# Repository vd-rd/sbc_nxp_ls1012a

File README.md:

# sbc-ls1012a
NXP Layerscape LS1012A

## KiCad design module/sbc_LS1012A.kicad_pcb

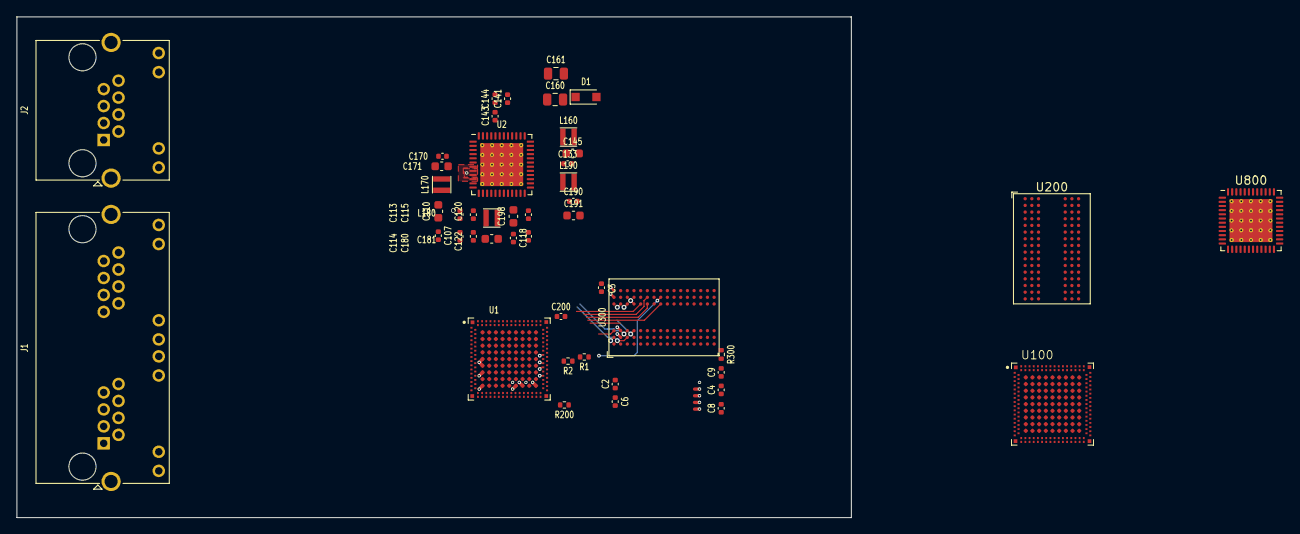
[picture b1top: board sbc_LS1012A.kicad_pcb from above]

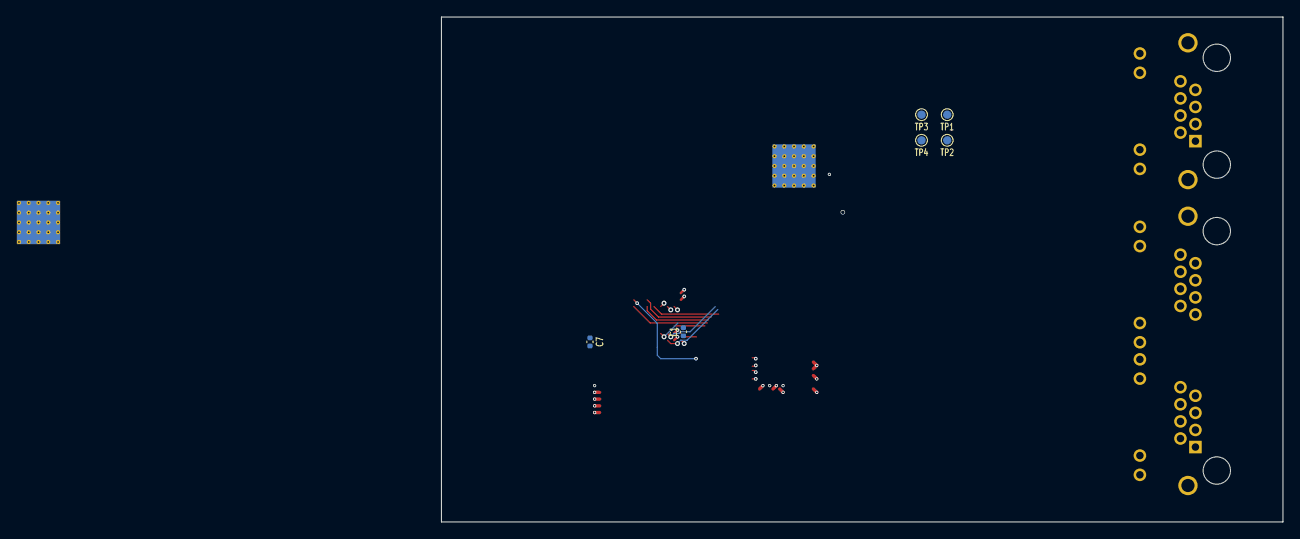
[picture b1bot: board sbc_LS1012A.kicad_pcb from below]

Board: 4 copper layers, 100.0 x 60.0 mm, 52 parts (6 on the bottom side), 87 nets.

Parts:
C1, C2, C3, C4, C9, C107, C118, C170, C180, C190, C200: 100nF; C_0402_1005Metric
C6, C7, C8, C113, C141, C143: 1uF; C_0402_1005Metric
C110, C171, C181, C191, C198: 4.7uF; C_0603_1608Metric
C114, C115, C120, C122, C133: 2.2uF; C_0402_1005Metric
C144: 220nF; C_0402_1005Metric
C145: 10uF; C_0603_1608Metric
C160, C161: 22uF; C_0805_2012Metric
D1: D_Schottky; D_SOD-323_HandSoldering
J1: RJ45_LED_Shielded_x2; RJ45_Amphenol_RJHSE538X-02
J2: RJ45_LED; RJ45_Amphenol_RJHSE538X
L160, L170, L180, L190: 1.5uH; L_Taiyo-Yuden_NR-20xx
R1, R2: 10; R_0402_1005Metric
R200, R300: 240; R_0402_1005Metric
TP1, TP2, TP3, TP4: TestPoint; TestPoint_Pad_D1.0mm
U1, U100: LS1012A; NXP_LS1012ASE7EKA
U2, U800: VR5100; QFN-48-1EP_7x7mm_P0.5mm_EP5.15x5.15mm_ThermalVias
U200, U300: MT41K512M16HA; BGA-96_9.0x13.0mm_Layout2x3x16_P0.8mm

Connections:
+3V3: C107.1, C110.1, C113.1, C118.1, C145.1, C198.1, L160.2, U2.7 (PVIN1), U2.10 (PVIN1), U2.13 (VLDOIN1), U2.16 (VLDOIN2), U2.18 (PVIN2), U2.21 (VLDOIN34), U2.28 (PVIN3), U2.38 (PVIN2), U2.42 (VIN), U800.7 (PVIN1), U800.10 (PVIN1), U800.13 (VLDOIN1), U800.16 (VLDOIN2), U800.18 (PVIN2), U800.21 (VLDOIN34), U800.28 (PVIN3), U800.38 (PVIN2), U800.42 (VIN)
/power/LDO2: C115.1, U2.15 (LDO2), U800.15 (LDO2)
/power/LDO3: C120.1, U2.20 (LDO3), U800.20 (LDO3)
/power/LDO4: C122.1, U2.22 (LDO4), U800.22 (LDO4)
/power/VDD_SFP: C114.1, U2.14 (LDO1), U800.14 (LDO1)
/power/lx1: L170.1, U2.8 (LX1), U2.9 (LX1), U800.8 (LX1), U800.9 (LX1)
/power/vr_vcc: C141.1, U2.41 (VCC), U800.41 (VCC)
/sdram/addr0: U1.103 (D1_MA00), U100.103 (D1_MA00), U200.N3 (A0), U300.N3 (A0)
/sdram/addr1: U1.37 (D1_MA01), U100.37 (D1_MA01), U200.P7 (A1), U300.P7 (A1)
/sdram/addr2: U1.102 (D1_MA02), U100.102 (D1_MA02), U200.P3 (A2), U300.P3 (A2)
/sdram/addr3: U1.97 (D1_MA03), U100.97 (D1_MA03), U200.N2 (A3), U300.N2 (A3)
/sdram/addr4: U1.98 (D1_MA04), U100.98 (D1_MA04), U200.P8 (A4), U300.P8 (A4)
/sdram/addr5: U1.38 (D1_MA05), U100.38 (D1_MA05), U200.P2 (A5), U300.P2 (A5)
/sdram/addr6: U1.34 (D1_MA06), U100.34 (D1_MA06), U200.R8 (A6), U300.R8 (A6)
/sdram/addr7: U1.32 (D1_MA07), U100.32 (D1_MA07), U200.R2 (A7), U300.R2 (A7)
/sdram/addr8: U1.96 (D1_MA08), U100.96 (D1_MA08), U200.T8 (A8), U300.T8 (A8)
/sdram/addr9: U1.100 (D1_MA09), U100.100 (D1_MA09), U200.R3 (A9), U300.R3 (A9)
/sdram/addr10: U1.106 (D1_MA10), U100.106 (D1_MA10), U200.L7 (A10/AP), U300.L7 (A10/AP)
/sdram/addr11: U1.99 (D1_MA11), U100.99 (D1_MA11), U200.R7 (A11), U300.R7 (A11)
/sdram/addr12: U1.40 (D1_MA12), U100.40 (D1_MA12), U200.N7 (A12/~BC), U300.N7 (A12/~BC)
/sdram/addr13: U1.33 (D1_MA13), U100.33 (D1_MA13), U200.T3 (A13), U300.T3 (A13)
/sdram/addr14: U1.31 (D1_MA14), U100.31 (D1_MA14), U200.T7 (A14), U300.T7 (A14)
/sdram/data0: U1.47 (D1_MDQ00), U100.47 (D1_MDQ00), U200.E3 (DQ0), U300.E3 (DQ0)
/sdram/data1: U1.50 (D1_MDQ01), U100.50 (D1_MDQ01), U200.F7 (DQ1), U300.F7 (DQ1)
/sdram/data2: U1.49 (D1_MDQ02), U100.49 (D1_MDQ02), U200.F2 (DQ2), U300.F2 (DQ2)
/sdram/data3: U1.114 (D1_MDQ03), U100.114 (D1_MDQ03), U200.F8 (DQ3), U300.F8 (DQ3)
/sdram/data4: U1.109 (D1_MDQ04), U100.109 (D1_MDQ04), U200.H3 (DQ4), U300.H3 (DQ4)
/sdram/data5: U1.46 (D1_MDQ05), U100.46 (D1_MDQ05), U200.H8 (DQ5), U300.H8 (DQ5)
/sdram/data6: U1.110 (D1_MDQ06), U100.110 (D1_MDQ06), U200.G2 (DQ6), U300.G2 (DQ6)
/sdram/data7: U1.113 (D1_MDQ07), U100.113 (D1_MDQ07), U200.H7 (DQ7), U300.H7 (DQ7)
/sdram/data8: U1.118 (D1_MDQ08), U100.118 (D1_MDQ08), U200.D7 (DQ8), U300.D7 (DQ8)
/sdram/data9: U1.116 (D1_MDQ09), U100.116 (D1_MDQ09), U200.C3 (DQ9), U300.C3 (DQ9)
/sdram/data10: U1.57 (D1_MDQ10), U100.57 (D1_MDQ10), U200.C8 (DQ10), U300.C8 (DQ10)
/sdram/data11: U1.53 (D1_MDQ11), U100.53 (D1_MDQ11), U200.C2 (DQ11), U300.C2 (DQ11)
/sdram/data12: U1.56 (D1_MDQ12), U100.56 (D1_MDQ12), U200.A7 (DQ12), U300.A7 (DQ12)
/sdram/data13: U1.51 (D1_MDQ13), U100.51 (D1_MDQ13), U200.A2 (DQ13), U300.A2 (DQ13)
/sdram/data14: U1.119 (D1_MDQ14), U100.119 (D1_MDQ14), U200.B8 (DQ14), U300.B8 (DQ14)
/sdram/data15: U1.115 (D1_MDQ15), U100.115 (D1_MDQ15), U200.A3 (DQ15), U300.A3 (DQ15)
/sdram/ddr_ba0: U1.101 (D1_MBA0), U100.101 (D1_MBA0), U200.M2 (BA0), U300.M2 (BA0)
/sdram/ddr_ba1: U1.36 (D1_MBA1), U100.36 (D1_MBA1), U200.N8 (BA1), U300.N8 (BA1)
/sdram/ddr_ba2: U1.104 (D1_MBA2), U100.104 (D1_MBA2), U200.M3 (BA2), U300.M3 (BA2)
/sdram/ddr_cas: U1.43 (D1_MCAS_B), U100.43 (D1_MCAS_B), U200.K3 (~CAS), U300.K3 (~CAS)
/sdram/ddr_ck_n: R2.1, U200.K7 (~CK), U300.K7 (~CK)
/sdram/ddr_ck_p: R1.1, U200.J7 (CK), U300.J7 (CK)
/sdram/ddr_cke: U1.42 (D1_MCKE), U100.42 (D1_MCKE), U200.K9 (CKE), U300.K9 (CKE)
/sdram/ddr_cs: U1.41 (D1_MCS_B), U100.41 (D1_MCS_B), U200.L2 (~CS), U300.L2 (~CS)
/sdram/ddr_dm0: U1.112 (D1_MDM0), U100.112 (D1_MDM0), U200.E7 (LDM), U300.E7 (LDM)
/sdram/ddr_dm1: U1.54 (D1_MDM1), U100.54 (D1_MDM1), U200.D3 (UDM), U300.D3 (UDM)
/sdram/ddr_dqs0+: U1.111 (D1_MDQS0), U100.111 (D1_MDQS0), U200.F3 (LDQS), U300.F3 (LDQS)
/sdram/ddr_dqs0-: U1.48 (D1_MDQS0_B), U100.48 (D1_MDQS0_B), U200.G3 (~LDQS), U300.G3 (~LDQS)
/sdram/ddr_dqs1+: U1.117 (D1_MDQS1), U100.117 (D1_MDQS1), U200.C7 (UDQS), U300.C7 (UDQS)
/sdram/ddr_dqs1-: U1.55 (D1_MDQS1_B), U100.55 (D1_MDQS1_B), U200.B7 (~UDQS), U300.B7 (~UDQS)
/sdram/ddr_odt: U1.45 (D1_MODT), U100.45 (D1_MODT), U200.K1 (ODT), U300.K1 (ODT)
/sdram/ddr_ras: U1.108 (D1_MRAS_B), U100.108 (D1_MRAS_B), U200.J3 (~RAS), U300.J3 (~RAS)
/sdram/ddr_we: U1.105 (D1_MWE_B), U100.105 (D1_MWE_B), U200.L3 (~WE), U300.L3 (~WE)
GND: C1.2, C2.2, C3.2, C4.2, C6.2, C7.2, C8.2, C9.2, C107.2, C110.2, C113.2, C114.2, C115.2, C118.2, C120.2, C122.2, C133.2, C141.2, C143.2, C144.2, C145.2, C160.2, C161.2, C170.2, C171.2, C180.2, C181.2, C190.2, C191.2, C198.2, C200.2, R200.1, R300.1, U1.131 (GND), U1.133 (GND), U1.135 (GND), U1.138 (GND), U1.139 (GND), U1.140 (GND), U1.146 (GND), U1.148 (GND), U1.150 (GND), U1.152 (GND), U1.153 (GND), U1.154 (GND), U1.156 (GND), U1.157 (GND), U1.158 (GND), U1.160 (GND), U1.162 (GND), U1.164 (GND), U1.166 (GND), U1.167 (GND), U1.170 (GND), U1.172 (GND), U1.175 (GND), U1.176 (GND), U1.178 (GND), U1.180 (GND), U1.182 (GND), U1.184 (GND), U1.185 (GND), U1.188 (GND), U1.190 (GND), U1.192 (GND), U1.193 (GND), U1.196 (XOSC_GND), U1.197 (SD_GND), U1.201 (SD_GND), U1.202 (GND), U1.203 (GND), U1.208 (SD_GND), U1.210 (GND), U1.211 (GND), U2.5 (ICTEST), U2.12 (SGND), U2.26 (SGND), U2.31 (SGND), U2.39 (VDDOTP), U2.40 (SGND), U2.49 (EP), U100.131 (GND), U100.133 (GND), U100.135 (GND), U100.138 (GND), U100.139 (GND), U100.140 (GND), U100.146 (GND), U100.148 (GND), U100.150 (GND), U100.152 (GND), U100.153 (GND), U100.154 (GND), U100.156 (GND), U100.157 (GND), U100.158 (GND), U100.160 (GND), U100.162 (GND), U100.164 (GND), U100.166 (GND), U100.167 (GND), U100.170 (GND), U100.172 (GND), U100.175 (GND), U100.176 (GND), U100.178 (GND), U100.180 (GND), U100.182 (GND), U100.184 (GND), U100.185 (GND), U100.188 (GND), U100.190 (GND), U100.192 (GND), U100.193 (GND), U100.196 (XOSC_GND), U100.197 (SD_GND), U100.201 (SD_GND), U100.202 (GND), U100.203 (GND), U100.208 (SD_GND), U100.210 (GND), U100.211 (GND), U200.A9 (VSS), U200.B1 (VSSQ), U200.B3 (VSS), U200.B9 (VSSQ), U200.D1 (VSSQ), U200.D8 (VSSQ), U200.E1 (VSS), U200.E2 (VSSQ), U200.E8 (VSSQ), U200.F9 (VSSQ), U200.G1 (VSSQ), U200.G8 (VSS), U200.G9 (VSSQ), U200.J2 (VSS), U200.J8 (VSS), U200.M1 (VSS), U200.M9 (VSS), U200.P1 (VSS), U200.P9 (VSS), U200.T1 (VSS), U200.T9 (VSS), U300.A9 (VSS), U300.B1 (VSSQ), U300.B3 (VSS), U300.B9 (VSSQ), U300.D1 (VSSQ), U300.D8 (VSSQ), U300.E1 (VSS), U300.E2 (VSSQ), U300.E8 (VSSQ), U300.F9 (VSSQ), U300.G1 (VSSQ), U300.G8 (VSS), U300.G9 (VSSQ), U300.J2 (VSS), U300.J8 (VSS), U300.M1 (VSS), U300.M9 (VSS), U300.P1 (VSS), U300.P9 (VSS), U300.T1 (VSS), U300.T9 (VSS), U800.5 (ICTEST), U800.12 (SGND), U800.26 (SGND), U800.31 (SGND), U800.39 (VDDOTP), U800.40 (SGND), U800.49 (EP)
unnamed: C143.1, U2.43 (VDIG), U800.43 (VDIG)
unnamed: C144.1, U2.44 (VBG), U800.44 (VBG)
unnamed: D1.2 (A), L160.1, U2.35 (LXBST), U800.35 (LXBST)
unnamed: L180.1, U2.17 (LX2), U800.17 (LX2)
unnamed: L190.1, U2.29 (LX3), U800.29 (LX3)
unnamed: R1.2, U1.44 (D1_MCK), U100.44 (D1_MCK)
unnamed: R2.2, U1.107 (D1_MCK_B), U100.107 (D1_MCK_B)
unnamed: R200.2, U1.35 (D1_MDIC), U100.35 (D1_MDIC)
unnamed: R300.2, U200.L8 (ZQ), U300.L8 (ZQ)
unnamed: U1.144 (O1VDD), U1.145 (O1VDD), U1.174 (O1VDD)
unnamed: U1.151 (VDD), U1.161 (VDD), U1.163 (VDD), U1.169 (VDD), U1.171 (VDD), U1.179 (VDD), U1.181 (VDD), U1.187 (VDD), U1.189 (VDD), U1.191 (VDD)
unnamed: U1.168 (O2VDD), U1.177 (O2VDD)
unnamed: U1.198 (S1VDD), U1.200 (S1VDD)
unnamed: U1.199 (X1VDD), U1.209 (X1VDD)
unnamed: U100.144 (O1VDD), U100.145 (O1VDD), U100.174 (O1VDD)
unnamed: U100.151 (VDD), U100.161 (VDD), U100.163 (VDD), U100.169 (VDD), U100.171 (VDD), U100.179 (VDD), U100.181 (VDD), U100.187 (VDD), U100.189 (VDD), U100.191 (VDD)
unnamed: U100.168 (O2VDD), U100.177 (O2VDD)
unnamed: U100.198 (S1VDD), U100.200 (S1VDD)
unnamed: U100.199 (X1VDD), U100.209 (X1VDD)
PMIC_I2C_SCL: TP3.1, U2.46 (SCL), U800.46 (SCL)
PMIC_I2C_SDA: TP2.1, U2.45 (SDA), U800.45 (SDA)
PMIC_INTn: TP1.1, U2.1 (INTb), U800.1 (INTb)
RESET: U200.T2 (~RESET), U300.T2 (~RESET)
SDHC_VSEL: TP4.1, U2.2 (SD_VSEL), U800.2 (SD_VSEL)
VCC_1V8: C180.1, C181.1, L180.2, U2.19 (FB2), U2.47 (VCCI2C), U800.19 (FB2), U800.47 (VCCI2C)
VCC_DDR: C1.1, C2.1, C3.1, C4.1, C6.1, C7.1, C8.1, C190.1, C191.1, L190.2, U1.147 (G1VDD), U1.155 (G1VDD), U1.165 (G1VDD), U1.173 (G1VDD), U1.183 (G1VDD), U2.24 (REFIN), U2.27 (FB3), U100.147 (G1VDD), U100.155 (G1VDD), U100.165 (G1VDD), U100.173 (G1VDD), U100.183 (G1VDD), U200.A1 (VDDQ), U200.A8 (VDDQ), U200.B2 (VDD), U200.C1 (VDDQ), U200.C9 (VDDQ), U200.D2 (VDDQ), U200.D9 (VDD), U200.E9 (VDDQ), U200.F1 (VDDQ), U200.G7 (VDD), U200.H2 (VDDQ), U200.H9 (VDDQ), U200.K2 (VDD), U200.K8 (VDD), U200.N1 (VDD), U200.N9 (VDD), U200.R1 (VDD), U200.R9 (VDD), U300.A1 (VDDQ), U300.A8 (VDDQ), U300.B2 (VDD), U300.C1 (VDDQ), U300.C9 (VDDQ), U300.D2 (VDDQ), U300.D9 (VDD), U300.E9 (VDDQ), U300.F1 (VDDQ), U300.G7 (VDD), U300.H2 (VDDQ), U300.H9 (VDDQ), U300.K2 (VDD), U300.K8 (VDD), U300.N1 (VDD), U300.N9 (VDD), U300.R1 (VDD), U300.R9 (VDD), U800.24 (REFIN), U800.27 (FB3)
VCC_DRAM_REF: C200.1, U1.52 (D1_MVREF), U100.52 (D1_MVREF)
VCC_OTG: C160.1, C161.1, D1.1 (K), U2.37 (FBBST), U800.37 (FBBST)
VCC_SD: C133.1, U2.33 (VSD), U800.33 (VSD)
VDD_CORE: C170.1, C171.1, L170.2, U2.6 (FB1), U800.6 (FB1)
VREF_DDR: C9.1, U200.H1 (VREFDQ), U200.M8 (VREFCA), U300.H1 (VREFDQ), U300.M8 (VREFCA)

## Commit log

2021-02-14 project: initial bringup
2021-02-16 project: add pmic
2021-04-27 add gitignore for kicad
2021-04-27 switch project to kicad
2021-04-28 add attributes
2021-04-28 reorg project structure
2021-10-20 updated project
2022-01-03 bump kicad 6
2022-06-29 update project
